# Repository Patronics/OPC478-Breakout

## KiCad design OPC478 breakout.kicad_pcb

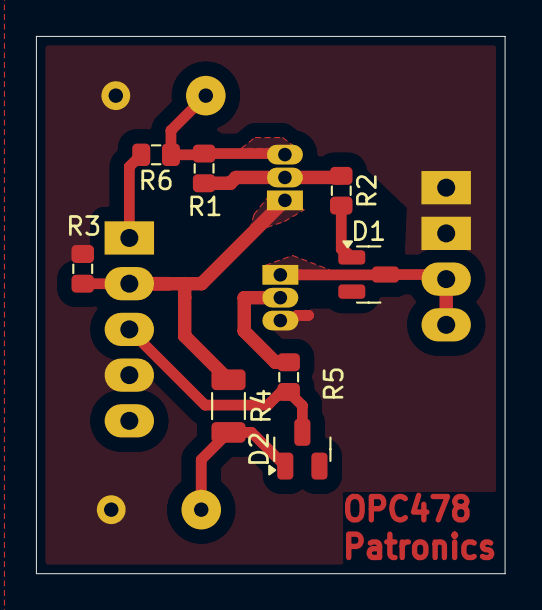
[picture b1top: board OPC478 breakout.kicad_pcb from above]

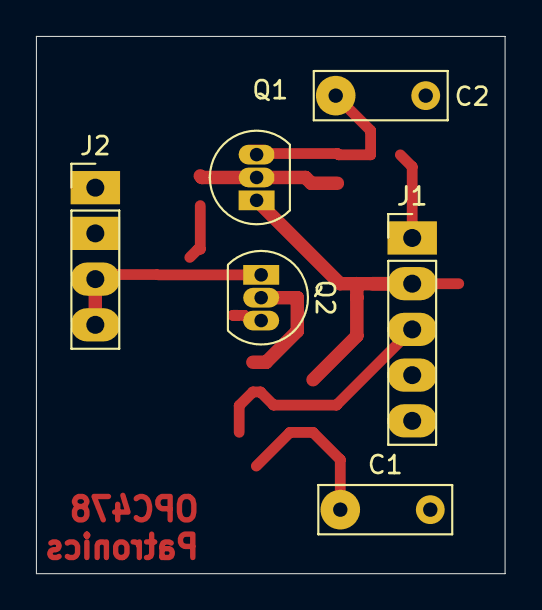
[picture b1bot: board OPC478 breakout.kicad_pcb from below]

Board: 2 copper layers, 26.0 x 29.8 mm, 14 parts (6 on the bottom side), 10 nets.

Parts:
C1: 0.47µF; C_Rect_L7.2mm_W2.5mm_P5.00mm_FKS2_FKP2_MKS2_MKP2
C2: 1µF; C_Rect_L7.2mm_W2.5mm_P5.00mm_FKS2_FKP2_MKS2_MKP2
D1, D2: 1N4148; SOT-23
J1: Conn_01x05_Pin; PinHeader_1x05_P2.54mm_Vertical
J2: AudioPlug4; PinHeader_1x04_P2.54mm_Vertical
Q1: BC557; TO-92_Inline
Q2: BC547; TO-92_Inline
R1, R2: 33k; R_0603_1608Metric
R3: 47k; R_0603_1608Metric
R4: 4k7; R_1206_3216Metric
R5: 15k; R_0603_1608Metric
R6: 150R; R_0603_1608Metric

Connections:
GND: C1.2, C2.2, J1.4, J2.S, Q2.3 (E), R3.2
unnamed: D1.1 (A), R2.2
unnamed: D1.3 (K), J2.R1, Q2.1 (C)
unnamed: C1.1, D2.1 (A), R4.2
unnamed: D2.3 (K), J1.3, R5.1
unnamed: J1.1, R6.2
unnamed: J1.2, Q1.1 (C), R3.1, R4.1
unnamed: Q1.2 (B), R1.2, R2.1
unnamed: C2.1, Q1.3 (E), R1.1, R6.1
unnamed: Q2.2 (B), R5.2

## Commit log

2025-02-13 initial commit of source files, first pass at functional PCB
2025-02-17 compacted and simplified layout, widened traces, first viable board produced
2025-02-17 remove no-longer needed jumper from schematic
2025-02-17 widened angled track that was challenging to cleanly machine
2025-02-17 adjust component layers to better match physical assembly
2025-02-17 further widen pads and traces to improve ease of milling and soldering
2025-02-22 improve milling speed and other minot changes
